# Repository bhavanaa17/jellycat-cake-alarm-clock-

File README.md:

# JELLYCAT CAKE ALARM CLOCK
An alarm clock inspired by the Jellycat Cake stuffed animal with 5 switches, a buzzer, and a display that displays the time. On top of the cake/alarm, there will be a light up candle that lights up at the end of your timers or alarms as a celebration. 

This alarm clock is inspired by the iconic Jellycat Cake stuffed animal. I wanted this project to be fun to make as this is my first ever project in HackClub. In addition, I really wanted to stick to the theme of "slumber" as we are making alarm clocks and getting pillowcase out of this, so might as well make look like a stuffed animal :) 
I learned so much from this project from learning how to use Github to creating my own pcb. This project was so fun to do and I'm so grateful that I was apart of the blare program!

# BOM
| NO. | Component                     | Quantity | Price | link                    |   |   |
|-----|-------------------------------|----------|-------|-------------------------|---|---|
| 1   | Switches & Keycaps            | 5        | ?     | ?                       |   |   |
| 2   | Lolin C3 Mini ESP 32 Devboard | 1        | ?     | ?                       |   |   |
| 3   | 3.3V Piezo Buzzer             | 1        | ?     | ?                       |   |   |
| 4   | 2.25in TFT Screen             | 1        | ?     | ?                       |   |   |
| 5   | 1K Ohm Resistor               | 1        | $3.99 | https://a.co/d/0bcCZgvA |   |   |
| 6   | MPS2222A NPN Transistor       | 1        | $5.29 | https://a.co/d/0cQcJC6b |   |   |
| 7   | Flickering Flame LED Bulb     | 1        | $5.79 | https://a.co/d/05IgeI5d |   |   |
| 8   | JST Connector                 | 1        | $5.97 | https://a.co/d/0f5pG4NX |   |   |

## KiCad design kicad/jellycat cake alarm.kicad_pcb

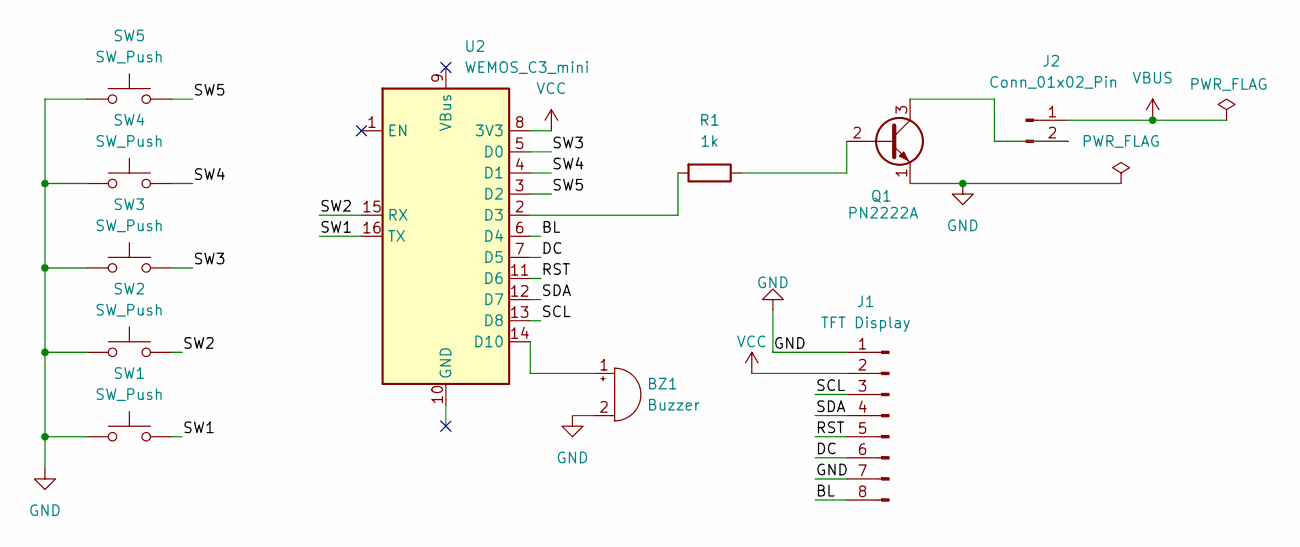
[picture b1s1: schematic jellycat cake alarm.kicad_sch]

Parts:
BZ1: Buzzer
J1: TFT Display; Display_ST7789_2.25in_76x284_8P
J2: Conn_01x02_Pin; JST_PH_B2B-PH-K_1x02_P2.00mm_Vertical
Q1: PN2222A; TO-92_Inline
R1: 1k; R_Axial_DIN0207_L6.3mm_D2.5mm_P10.16mm_Horizontal
SW1, SW2, SW3, SW4, SW5: SW_Push; SW_MX_1u
U2: WEMOS_C3_mini

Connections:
/BL: J1.8, U2.6 (D4)
/DC: J1.6, U2.7 (D5)
/RST: J1.5, U2.11 (D6)
/SCL: J1.3, U2.13 (D8)
/SDA: J1.4, U2.12 (D7)
/SW1: SW1.2, U2.16 (TX)
/SW2: SW2.2, U2.15 (RX)
/SW3: SW3.2, U2.5 (D0)
/SW4: SW4.2, U2.4 (D1)
/SW5: SW5.2, U2.3 (D2)
GND: BZ1.2 (-), J1.1, J1.7, Q1.1 (E), SW1.1, SW2.1, SW3.1, SW4.1, SW5.1
unnamed: BZ1.1 (+), U2.14 (D10)
unnamed: J2.2, Q1.3 (C)
unnamed: Q1.2 (B), R1.1
unnamed: R1.2, U2.2 (D3)
VBUS: J2.1
VCC: J1.2, U2.8 (3V3)

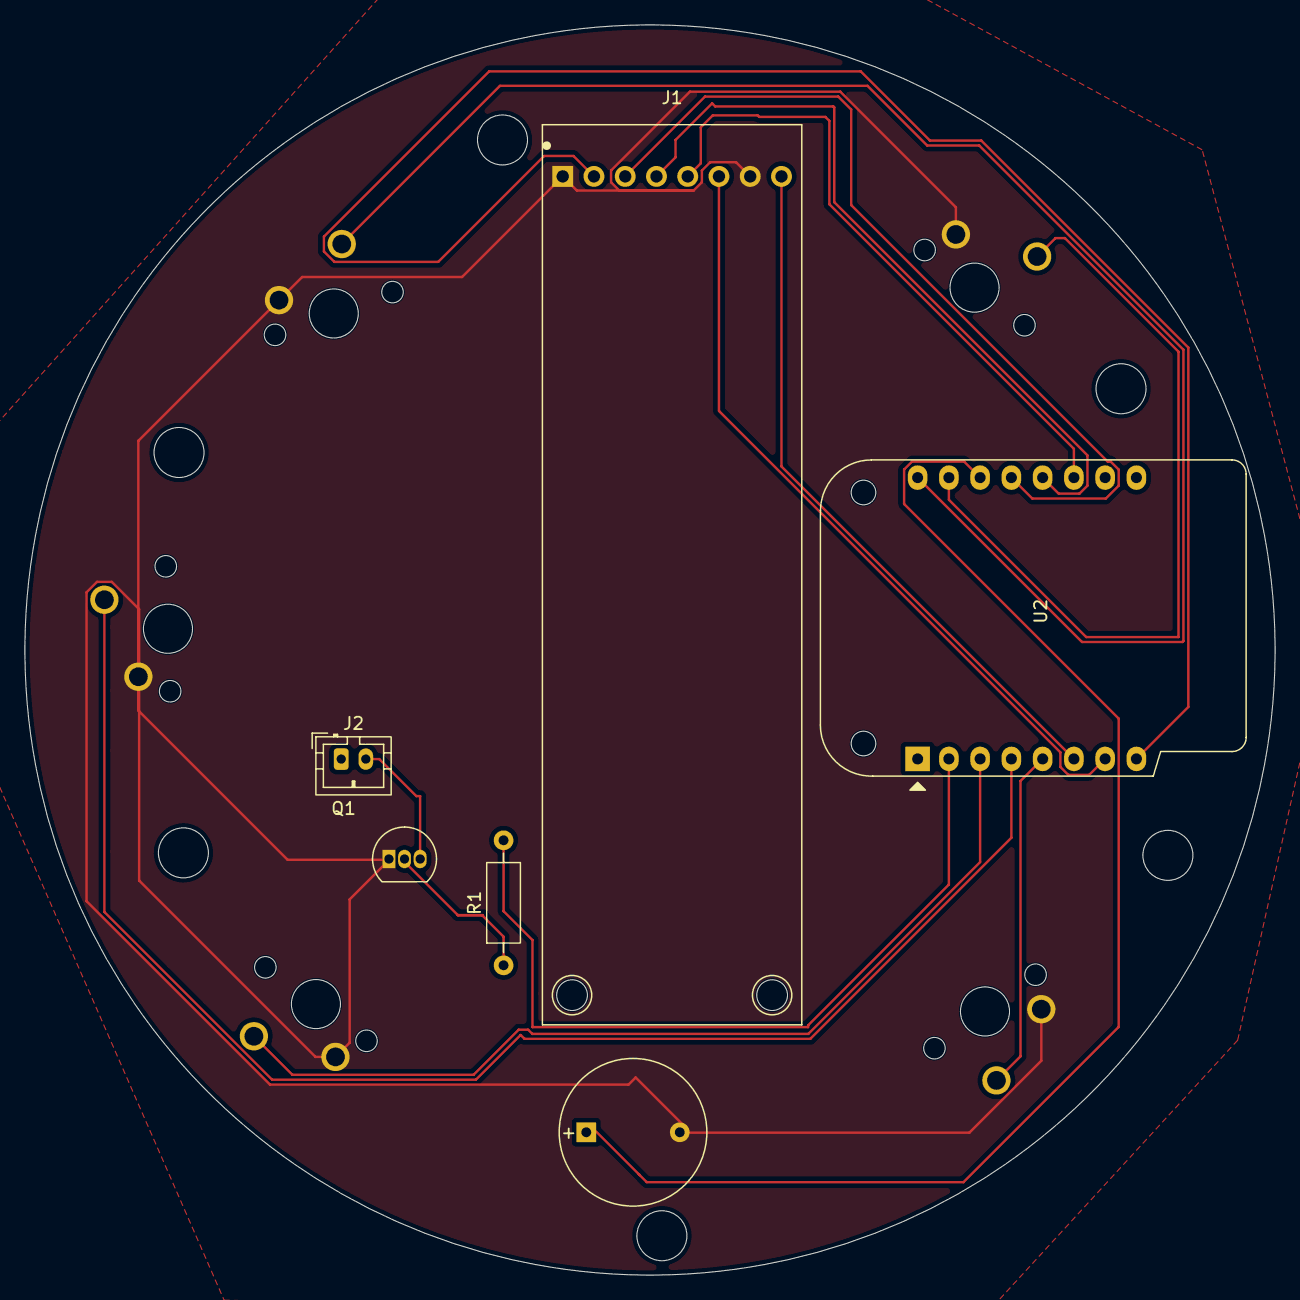
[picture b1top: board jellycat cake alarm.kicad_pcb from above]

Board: 2 copper layers, 101.6 x 101.6 mm, 11 parts (0 on the bottom side), 16 nets.
